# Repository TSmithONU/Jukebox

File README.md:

# Jukebox
This is the code and diagram to the Blue Jukebox located in COSI's Progress exhibit. Blue runs on an Arduino Mega and an Adafruit VS1053 Breakout board. This exhibit allows users to select a track number, and the corresponding track is played. To accomplish this, the mega reads in button presses from the button array on the front of the jukebox. The Mega then uses serial communication to begin playback of the track. Relay control was added to control the button latching and record spinning during playback. There is also a reset button that ends playback and resets the VS1053.

This software is designed to work with any Mega and can be costomized to playback any mp3 file.

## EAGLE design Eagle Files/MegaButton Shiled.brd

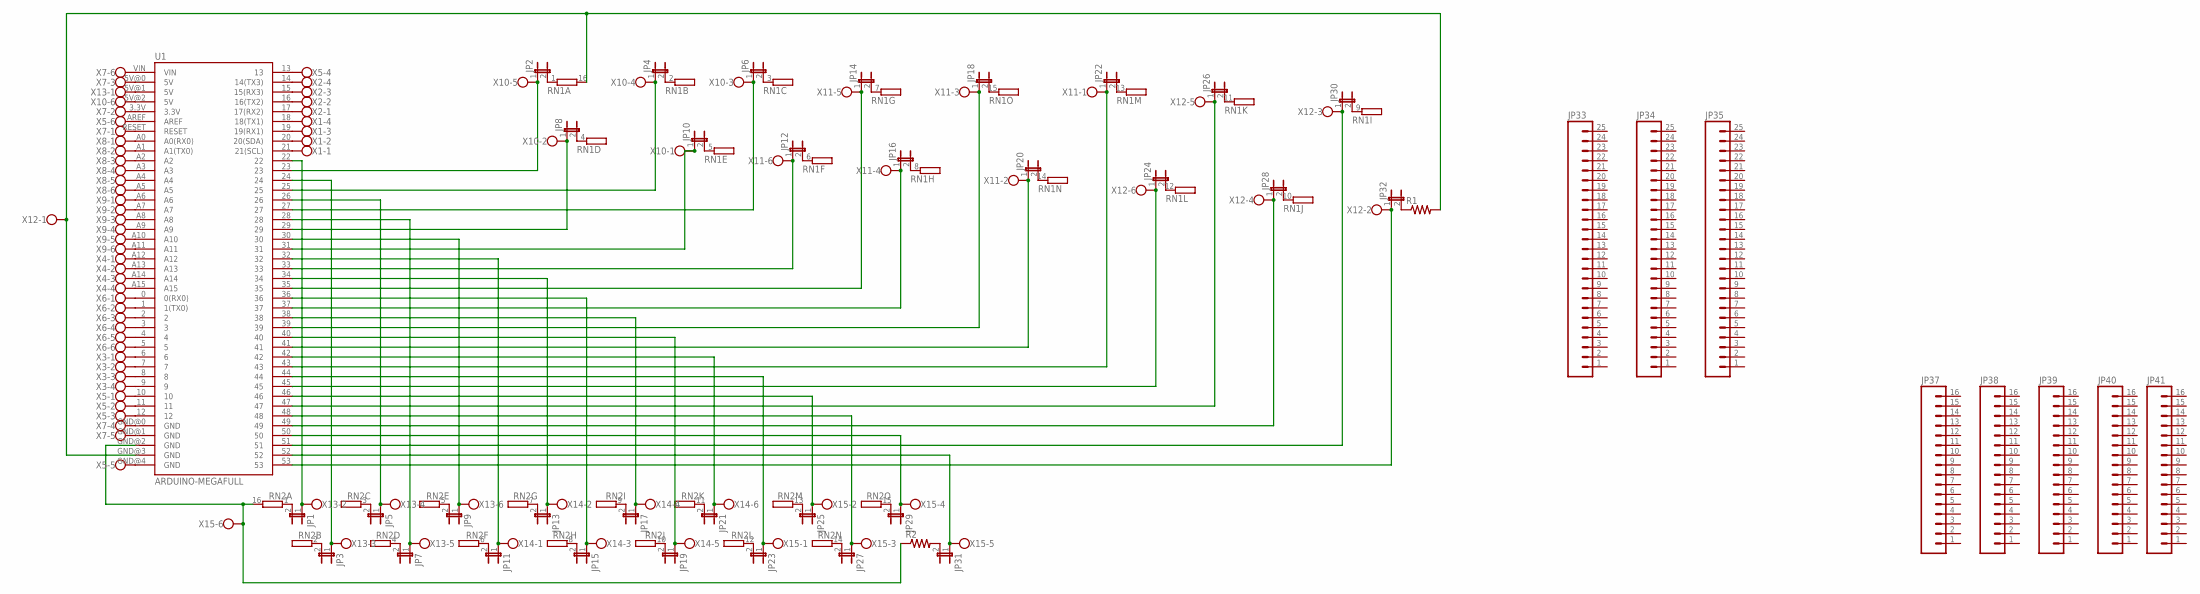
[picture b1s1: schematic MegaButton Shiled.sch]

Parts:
JP1, JP2, JP3, JP4, JP5, JP6, JP7, JP8, JP9, JP10, JP11, JP12, JP13, JP14, JP15, JP16, JP17, JP18, JP19, JP20, JP21, JP22, JP23, JP24, JP25, JP26, JP27, JP28, JP29, JP30, JP31, JP32: JP1E; JP1
JP33, JP34, JP35: M25PTH; 1X25
JP37, JP38, JP39, JP40, JP41: M16PTH; 1X16
R1, R2: R-US_0204/5; 0204/5
RN1, RN2: E15R; DIL16
U1: ARDUINO-MEGAFULL; ARDUINO_MEGA
X1, X2, X3, X4: W237-4
X5, X6, X7: W237-136
X8, X9, X10, X11, X12, X13, X14, X15: W237-6

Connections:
unnamed: U1.18 (18(TX1)), X1.4
unnamed: U1.19 (19(RX1)), X1.3
unnamed: U1.20 (20(SDA)), X1.2
unnamed: U1.21 (21(SCL)), X1.1
unnamed: U1.14 (14(TX3)), X2.4
unnamed: U1.15 (15(RX3)), X2.3
unnamed: U1.16 (16(TX2)), X2.2
unnamed: U1.17 (17(RX2)), X2.1
unnamed: U1.0 (0(RX0)), X6.1
unnamed: U1.1 (1(TX0)), X6.2
unnamed: U1.2, X6.3
unnamed: U1.3, X6.4
unnamed: U1.4, X6.5
unnamed: U1.5, X6.6
unnamed: U1.6, X3.1
unnamed: U1.7, X3.2
unnamed: U1.8, X3.3
unnamed: U1.9, X3.4
unnamed: U1.10, X5.1
unnamed: U1.11, X5.2
unnamed: U1.12, X5.3
unnamed: U1.13, X5.4
unnamed: U1.GND@4 (GND), X5.5
unnamed: U1.AREF, X5.6
unnamed: U1.RESET, X7.1
unnamed: U1.3.3V, X7.2
unnamed: U1.5V@0 (5V), X7.3
unnamed: U1.GND@0 (GND), X7.4
unnamed: U1.GND@1 (GND), X7.5
unnamed: U1.VIN, X7.6
unnamed: U1.A0 (A0(RX0)), X8.1
unnamed: U1.A1 (A1(TX0)), X8.2
unnamed: U1.A2, X8.3
unnamed: U1.A3, X8.4
unnamed: U1.A4, X8.5
unnamed: U1.A5, X8.6
unnamed: U1.A6, X9.1
unnamed: U1.A7, X9.2
unnamed: U1.A8, X9.3
unnamed: U1.A9, X9.4
unnamed: U1.A10, X9.5
unnamed: U1.A11, X9.6
unnamed: U1.A12, X4.1
unnamed: U1.A13, X4.2
unnamed: U1.A14, X4.3
unnamed: U1.A15, X4.4
unnamed: U1.5V@2 (5V), X10.6
unnamed: JP2.2, RN1.1
unnamed: JP2.1, U1.23, X10.5
unnamed: JP1.1, U1.22, X13.2
unnamed: JP4.1, U1.25, X10.4
unnamed: JP4.2, RN1.2 (1)
unnamed: JP6.1, U1.27, X10.3
unnamed: JP6.2, RN1.3 (1)
unnamed: JP8.1, U1.29, X10.2
unnamed: JP8.2, RN1.4 (1)
unnamed: JP10.1, U1.31, X10.1
unnamed: JP10.2, RN1.5 (1)
unnamed: JP12.1, U1.33, X11.6
unnamed: JP12.2, RN1.6 (1)
unnamed: JP14.2, RN1.7 (1)
unnamed: JP14.1, U1.35, X11.5
unnamed: JP16.2, RN1.8 (1)
unnamed: JP16.1, U1.37, X11.4
unnamed: JP18.2, RN1.15 (1)
unnamed: JP18.1, U1.39, X11.3
unnamed: JP20.1, U1.41, X11.2
unnamed: JP20.2, RN1.14 (1)
unnamed: JP22.1, U1.43, X11.1
unnamed: JP22.2, RN1.13 (1)
unnamed: JP24.1, U1.45, X12.6
unnamed: JP24.2, RN1.12 (1)
unnamed: JP26.2, RN1.11 (1)
unnamed: JP26.1, U1.47, X12.5
unnamed: JP28.2, RN1.10 (1)
unnamed: JP28.1, U1.49, X12.4
unnamed: JP30.2, RN1.9 (1)
unnamed: JP30.1, U1.51, X12.3
unnamed: JP32.1, U1.53, X12.2
unnamed: JP32.2, R1.1
unnamed: JP1.2, RN2.1
unnamed: U1.5V@1 (5V), X13.1
unnamed: JP3.2, RN2.2 (1)
unnamed: JP3.1, U1.24, X13.3
unnamed: JP5.2, RN2.3 (1)
unnamed: JP5.1, U1.26, X13.4
unnamed: JP7.2, RN2.4 (1)
unnamed: JP7.1, U1.28, X13.5
unnamed: JP9.2, RN2.5 (1)
unnamed: JP9.1, U1.30, X13.6
unnamed: JP11.2, RN2.6 (1)
unnamed: JP11.1, U1.32, X14.1
unnamed: JP13.2, RN2.7 (1)
unnamed: JP13.1, U1.34, X14.2
unnamed: JP15.2, RN2.8 (1)
unnamed: JP15.1, U1.36, X14.3
unnamed: JP17.2, RN2.9 (1)
unnamed: JP17.1, U1.38, X14.4
unnamed: JP19.2, RN2.10 (1)
unnamed: JP19.1, U1.40, X14.5
unnamed: JP21.2, RN2.11 (1)
unnamed: JP21.1, U1.42, X14.6
unnamed: JP23.2, RN2.12 (1)
unnamed: JP23.1, U1.44, X15.1
unnamed: JP25.2, RN2.13 (1)
unnamed: JP25.1, U1.46, X15.2
unnamed: R1.2, RN1.16 (2), U1.GND@3 (GND), X12.1
unnamed: JP27.2, RN2.14 (1)
unnamed: JP27.1, U1.48, X15.3
unnamed: JP29.2, RN2.15 (1)
unnamed: JP29.1, U1.50, X15.4
unnamed: JP31.2, R2.2
unnamed: JP31.1, U1.52, X15.5
unnamed: R2.1, RN2.16 (2), U1.GND@2 (GND), X15.6

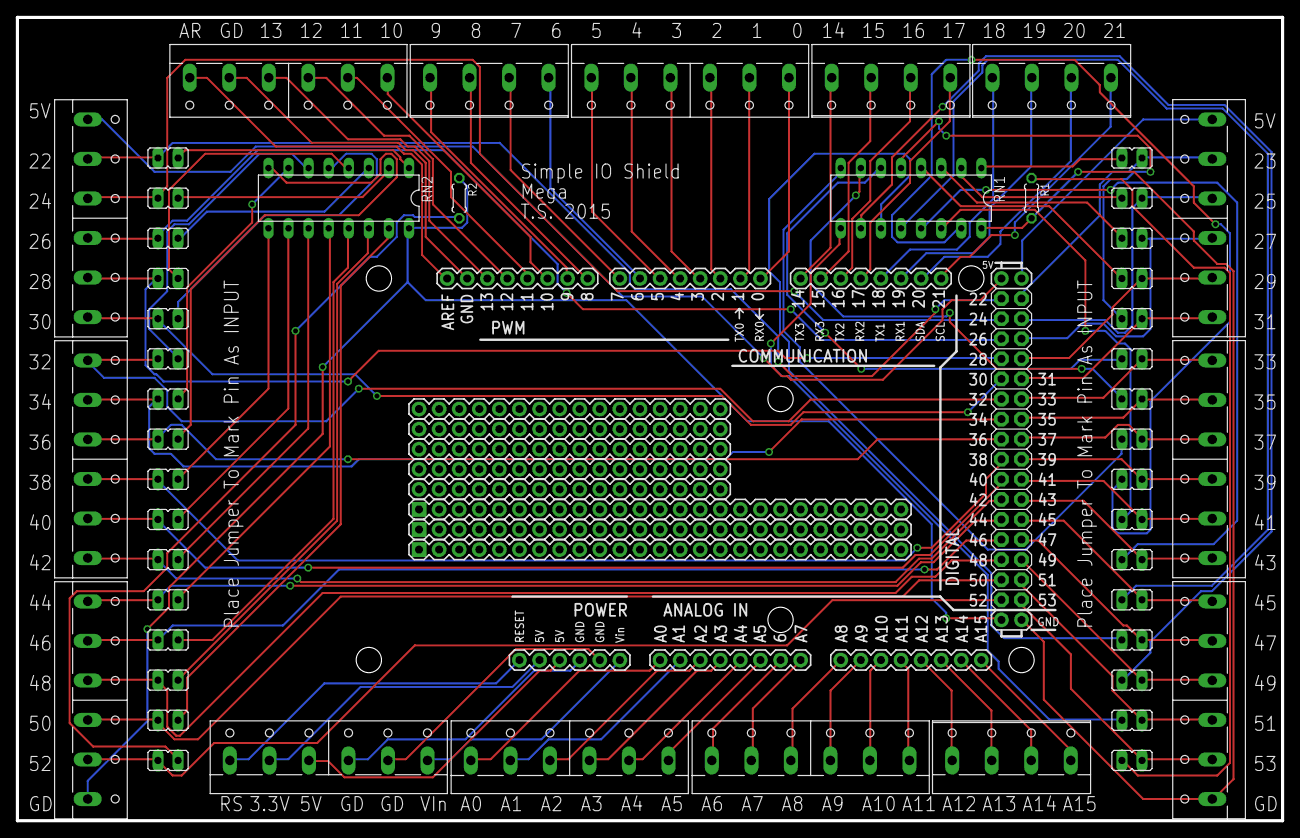
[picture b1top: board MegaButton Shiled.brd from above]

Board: 2 copper layers, 160.0 x 101.6 mm, 60 parts (0 on the bottom side), 114 nets.

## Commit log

2016-06-02 :space_invader: Added .gitattributes & .gitignore files
2016-06-02 Upload Code
    Initial Upload to github
2016-06-02 Add Schematic
    Uploading wiring schematic of jukebox

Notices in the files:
parts and their libraries:
SparkFun-Boards: Licensing: Creative Commons ShareAlike 4.0 International - https://creativecommons.org/licenses/by-sa/4.0
